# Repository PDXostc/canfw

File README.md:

# CAN FIREWALL

There are two tables, IVI2VEH and VEH2IVI, specifiying rules for
traffic going from the IVI to the vehicle and from vehicle to IVI.

Each one of the two tables has a number of rules.

Each rule has a numberic ID. Rules are executed in order of ascending IDs.

Each rule has an Frame ID mask and a Frame ID filter, applied
according to the standard CAN bus filter principle, as described 
[here](http://www.cse.dmu.ac.uk/~eg/tele/CanbusIDandMask.html).

Below is pseudo code for frame processing.

    process_frame(frame_id, payload) {

      // Traverse all rules
      for (i in rules) {
	    masked_id = (frame_id & rules[i].id_mask);

	    // If the masked out ID is 0, we have a hit. Process
        if (!masked_id) {
	      process(frame_id, input, rules[i].action,
		          rules[i].id_operand, rules[i].data_operand);
	      return;
	    }

        // Check if we have a hit on the masked ID and the
		// ID filter.
	    // If so, we have a hit and will process
	    if (masked_id & rules[i].id_filter) {
	      process(frame_id, input, rules[i].action,
		          rules[i].id_operand, rules[i].data_operand);
	      return;
	    }

        // No hit. Try next rule
	  }

	  // No rule matched. Forward unmodified frame
      process(frame_id, input, ID_AND_DATA_AND,
	          0xFFFFFFFF, 0xFFFFFFFFFFFFFFFF);

	  return ok;
    }

Below is an example of a rule table.

ID | IdMask     |   IdFilter | Action          | IdOperand  | DataOperand        |
---|------------|------------|-----------------|------------|--------------------|
1  | 0xFFFFFFFF | 0x00000012 | ID_AND_DATA_OR  | 0x00FFFFFF | 0x000000FFFFFFFFFF |
2  | 0xFFFFFFF0 | 0x00000120 | ID_SET_DATA_SET | 0x01234567 | 0x0123456780ABCDEF |
99 | 0x00000000 | 0x00000000 | BLOCK           | 0x00000000 | 0x0000000000000000 |

* **RULE 1**<br>
  Rule ID 1 specifies will filter out the lower all bits of the CAN
  frame ID and match those against the specific ID 0x12, thus intercepting
  all CAN frames with the exact ID of 0x00000012.<br>
  An intercepted frame will be forwarded to the other side after ANDing
  the incoming Frame ID with ```0x00FFFFFF```, and then ORing the
  data payload with ```0x000000FFFFFFFFFF```.<br>
  Once the intercepted frame has been forwarded, the next frame is processed.

* **RULE 2**<br>

  Rule ID 2 is evaluated for all frames not intercepted by Rule 1 above.
  The rule will mask the incoming CAN frame ID against ```0xFFFFFFF0```
  and filter the result against ```0x00000120```, intercepting all
  CAN frames between ```0x00000120``` and ```0x0000012F```.<br>
  For each frame intercetpted by rule 2, a fixed frame will be sent to the other side
  with the frame ID ```0x01234567``` and payload ```0x0123456780ABCDEF```.

* **RULE 99**<br>
  Rule 99, a catch all, has a mask that intercepts all frames not intercepted
  by rule 1 or 2. Since the mask is ```0x00000000```, the filter will not be
  used since there no bits will pass the mask to be applied to the filter.<br>
  Rule 99 will block the frame and not send anything to the other side.<br>
  The modification bitmasks for the frame ID and data payload are unused 
  for blocking rules.

Please see presentation under doc for further details.

Hardware Details and Data sheets:
AT32UC3C2512C Datasheet http://www.mouser.com/ds/2/36/doc32117-74889.pdf

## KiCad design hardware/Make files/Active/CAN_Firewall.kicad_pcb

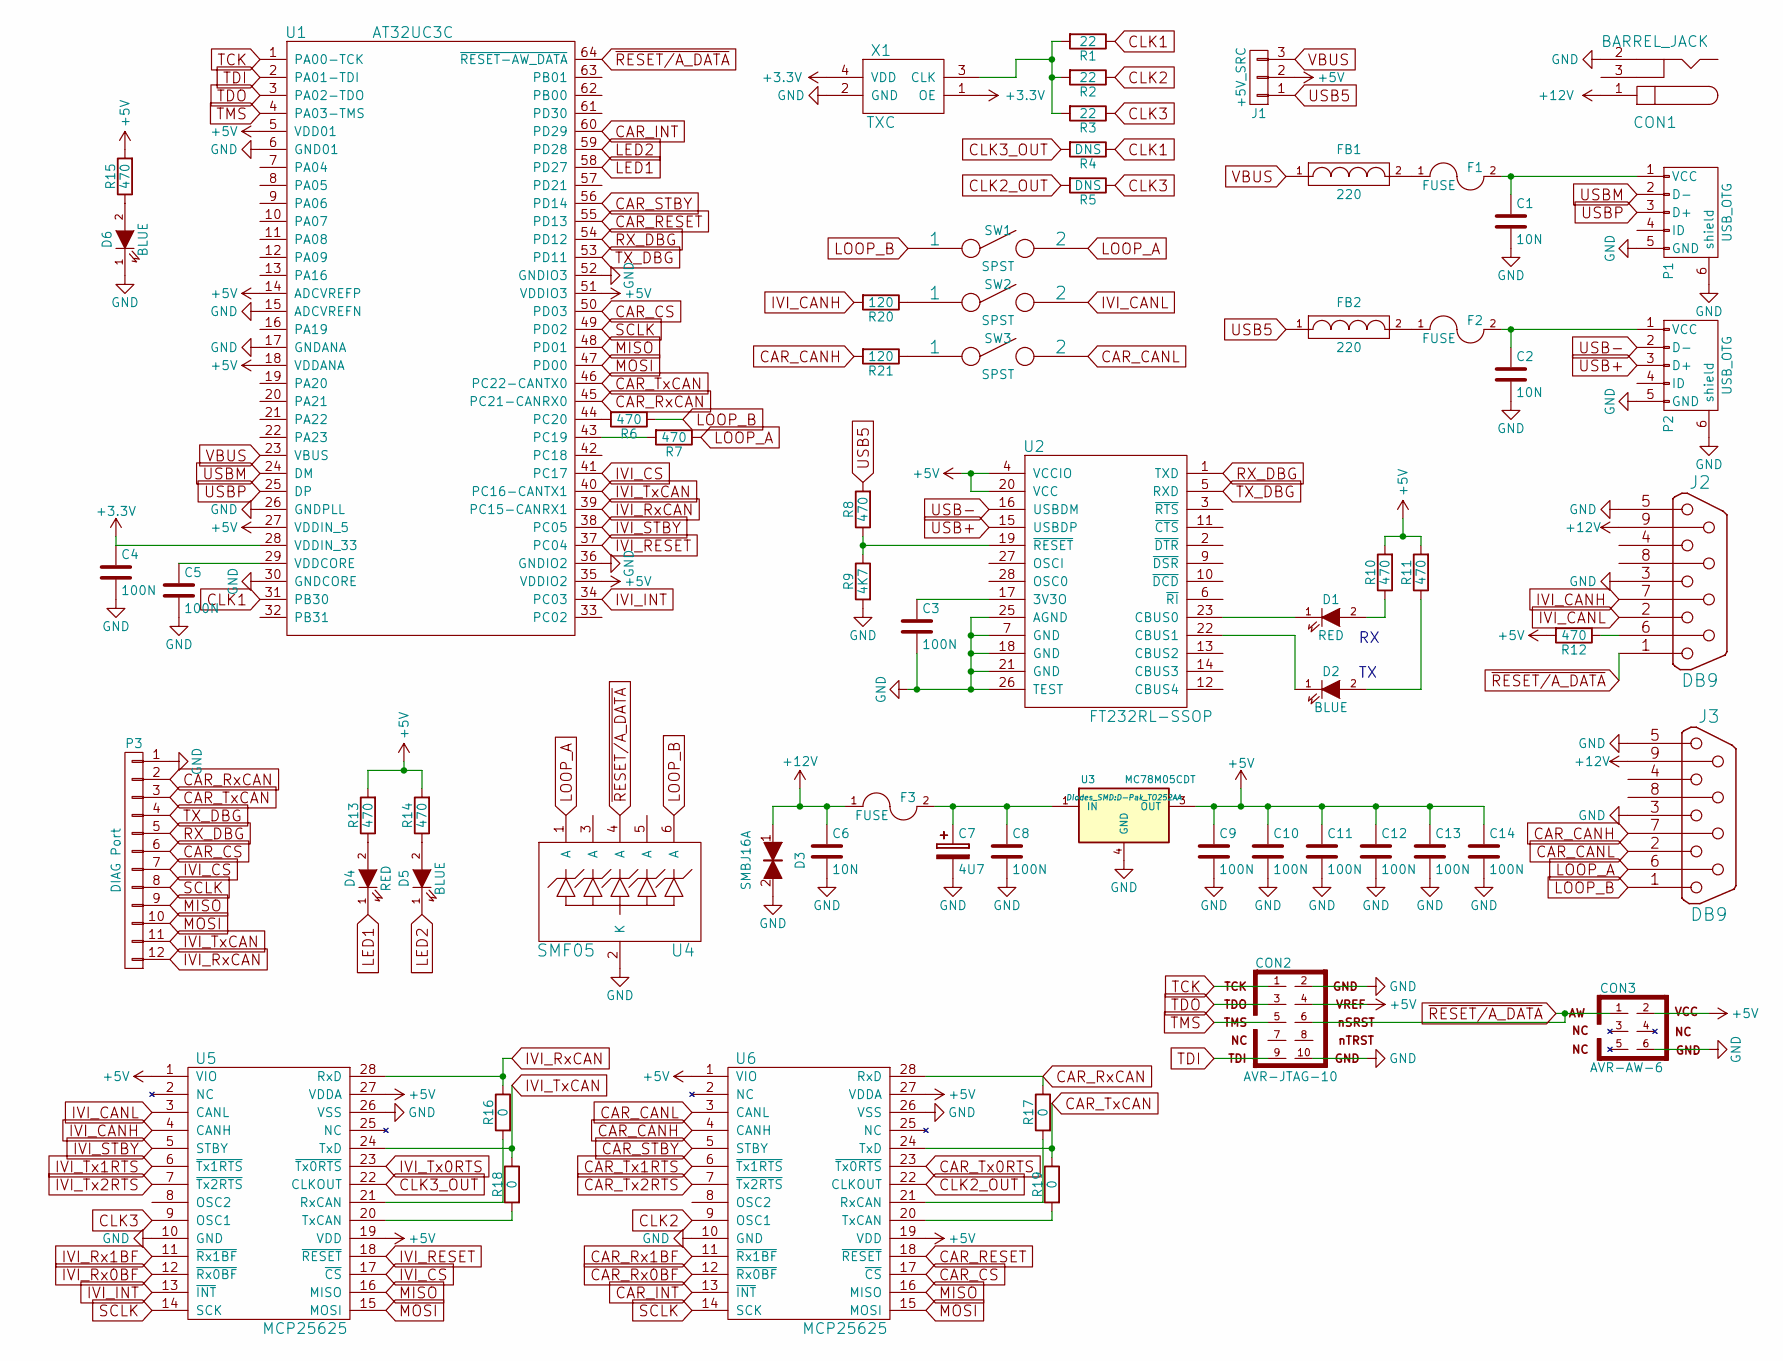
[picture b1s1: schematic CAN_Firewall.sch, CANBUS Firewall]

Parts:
C1, C2, C6: 10N; R_0603_sm
C3, C4, C5, C8, C9, C10, C11, C12, C13, C14: 100N; R_0603_sm
C7: 4U7; TantalC_SizeA_EIA-3216_Reflow
CON1: BARREL_JACK
CON2: AVR-JTAG-10; Socket_Strip_Straight_2x05
CON3: AVR-AW-6; Socket_Strip_Straight_2x03
D1, D4: RED; Diode_0805_12
D2, D5, D6: BLUE; Diode_0805_12
D3: SMBJ16A; SMB_Handsoldering
F1, F2, F3: FUSE; R_1210_SM
FB1, FB2: 220; Diode_0805_12_SM
J1: +5V_SRC; Socket_Strip_Straight_1x03
J2, J3: DB9; DB9F_CI
P1, P2: USB_OTG; USB_Micro-B-DX4R005JJ2R1800
P3: DIAG Port; Socket_Strip_Straight_1x12
R1, R2, R3: 22; R_0603_sm
R4, R5: DNS; R_0603_sm
R6, R7, R8, R10, R11, R12, R13, R14, R15: 470; R_0603_sm
R9: 4K7; R_0603_sm
R16, R17, R18, R19: 0; R_0603_sm
R20, R21: 120; R_0603_sm
SW1, SW2, SW3: SPST; SW_SPST_FSMSM_SM
U1: AT32UC3C; LQFP-64_10x10mm_Pitch0.5mm
U2: FT232RL-SSOP; SSOP-28_5.3x10.2mm_Pitch0.65mm
U3: MC78M05CDT; D-Pak_TO252AA
U4: SMF05; SC-70-6
U5, U6: MCP25625; SSOP-28_5.3x10.2mm_Pitch0.65mm
X1: TXC

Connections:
+3V3: C4.1, U1.28 (VDDIN_33), X1.1 (OE), X1.4 (VDD)
+5V: C9.1, C10.1, C11.1, C12.1, C13.1, C14.1, CON2.4, CON3.2, J1.2, R10.2, R11.2, R12.2, R13.2, R14.2, R15.2, U1.5 (VDD01), U1.14 (ADCVREFP), U1.18 (VDDANA), U1.27 (VDDIN_5), U1.35 (VDDIO2), U1.51 (VDDIO3), U2.4 (VCCIO), U2.20 (VCC), U3.3 (OUT), U5.1 (VIO), U5.19 (VDD), U5.27 (VDDA), U6.1 (VIO), U6.19 (VDD), U6.27 (VDDA)
+12V: C6.1, CON1.1, D3.1, F3.1, J2.9, J3.9
CAR_CANH: J3.7, R21.2, U6.4 (CANH)
CAR_CANL: J3.2, SW3.2, U6.3 (CANL)
CAR_CS: P3.6, U1.50 (PD03), U6.17 (~CS)
CAR_INT: U1.60 (PD29), U6.13 (~INT)
CAR_RESET: U1.55 (PD13), U6.18 (~RESET)
CAR_Rx0BF: U6.12 (~Rx0BF)
CAR_Rx1BF: U6.11 (~Rx1BF)
CAR_RxCAN: P3.2, R17.1, U1.45 (PC21-CANRX0), U6.28 (RxD)
CAR_STBY: U1.56 (PD14), U6.5 (STBY)
CAR_Tx0RTS: U6.23 (~Tx0RTS)
CAR_Tx1RTS: U6.6 (~Tx1RTS)
CAR_Tx2RTS: U6.7 (~Tx2RTS)
CAR_TxCAN: P3.3, R19.1, U1.46 (PC22-CANTX0), U6.24 (TxD)
CLK1: R1.1, R4.1, U1.31 (PB30)
CLK2: R2.1, U6.9 (OSC1)
CLK2_OUT: R5.2, U6.22 (CLKOUT)
CLK3: R3.1, R5.1, U5.9 (OSC1)
CLK3_OUT: R4.2, U5.22 (CLKOUT)
GND: C1.2, C2.2, C3.2, C4.2, C5.2, C6.2, C7.2, C8.2, C9.2, C10.2, C11.2, C12.2, C13.2, C14.2, CON1.2, CON2.2, CON2.10, CON3.6, D3.2, D6.1 (K), J2.3, J2.5, J3.3, J3.5, P1.5 (GND), P1.6 (shield), P2.5 (GND), P2.6 (shield), P3.1, R9.2, U1.6 (GND01), U1.15 (ADCVREFN), U1.17 (GNDANA), U1.26 (GNDPLL), U1.30 (GNDCORE), U1.36 (GNDIO2), U1.52 (GNDIO3), U2.7 (GND), U2.18 (GND), U2.21 (GND), U2.25 (AGND), U2.26 (TEST), U3.4 (GND), U4.2 (K), U5.10 (GND), U5.26 (VSS), U6.10 (GND), U6.26 (VSS), X1.2 (GND)
IVI_CANH: J2.7, R20.2, U5.4 (CANH)
IVI_CANL: J2.2, SW2.2, U5.3 (CANL)
IVI_CS: P3.7, U1.41 (PC17), U5.17 (~CS)
IVI_INT: U1.34 (PC03), U5.13 (~INT)
IVI_RESET: U1.37 (PC04), U5.18 (~RESET)
IVI_Rx0BF: U5.12 (~Rx0BF)
IVI_Rx1BF: U5.11 (~Rx1BF)
IVI_RxCAN: P3.12, R16.1, U1.39 (PC15-CANRX1), U5.28 (RxD)
IVI_STBY: U1.38 (PC05), U5.5 (STBY)
IVI_Tx0RTS: U5.23 (~Tx0RTS)
IVI_Tx1RTS: U5.6 (~Tx1RTS)
IVI_Tx2RTS: U5.7 (~Tx2RTS)
IVI_TxCAN: P3.11, R18.1, U1.40 (PC16-CANTX1), U5.24 (TxD)
LED1: D4.1 (K), U1.58 (PD27)
LED2: D5.1 (K), U1.59 (PD28)
LOOP_A: J3.6, R7.1, SW1.2, U4.1 (A)
LOOP_B: J3.1, R6.1, SW1.1, U4.6 (A)
MISO: P3.9, U1.48 (PD01), U5.16 (MISO), U6.16 (MISO)
MOSI: P3.10, U1.47 (PD00), U5.15 (MOSI), U6.15 (MOSI)
unnamed: C1.1, F1.2, P1.1 (VCC)
unnamed: C2.1, F2.2, P2.1 (VCC)
unnamed: C3.1, U2.17 (3V3O)
unnamed: C5.1, U1.29 (VDDCORE)
unnamed: C7.1, C8.1, F3.2, U3.1 (IN)
unnamed: D1.1 (K), U2.23 (CBUS0)
unnamed: D1.2 (A), R10.1
unnamed: D2.1 (K), U2.22 (CBUS1)
unnamed: D2.2 (A), R11.1
unnamed: D4.2 (A), R13.1
unnamed: D5.2 (A), R14.1
unnamed: D6.2 (A), R15.1
unnamed: F1.1, FB1.2
unnamed: F2.1, FB2.2
unnamed: J2.6, R12.1
unnamed: R1.2, R2.2, R3.2, X1.3 (CLK)
unnamed: R6.2, U1.44 (PC20)
unnamed: R7.2, U1.43 (PC19)
unnamed: R8.1, R9.1, U2.19 (~RESET)
unnamed: R16.2, U5.21 (RxCAN)
unnamed: R17.2, U6.21 (RxCAN)
unnamed: R18.2, U5.20 (TxCAN)
unnamed: R19.2, U6.20 (TxCAN)
unnamed: R20.1, SW2.1
unnamed: R21.1, SW3.1
RX_DBG: P3.5, U1.54 (PD12), U2.1 (TXD)
SCLK: P3.8, U1.49 (PD02), U5.14 (SCK), U6.14 (SCK)
TCK: CON2.1, U1.1 (PA00-TCK)
TDI: CON2.9, U1.2 (PA01-TDI)
TDO: CON2.3, U1.3 (PA02-TDO)
TMS: CON2.5, U1.4 (PA03-TMS)
TX_DBG: P3.4, U1.53 (PD11), U2.5 (RXD)
USB5: FB2.1, J1.1, R8.2
USB+: P2.3 (D+), U2.15 (USBDP)
USB-: P2.2 (D-), U2.16 (USBDM)
USBM: P1.2 (D-), U1.24 (DM)
USBP: P1.3 (D+), U1.25 (DP)
VBUS: FB1.1, J1.3, U1.23 (VBUS)
~RESET/A_DATA: CON2.6, CON3.1, J2.1, U1.64 (~RESET-AW_DATA), U4.4 (A)

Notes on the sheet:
RX TX

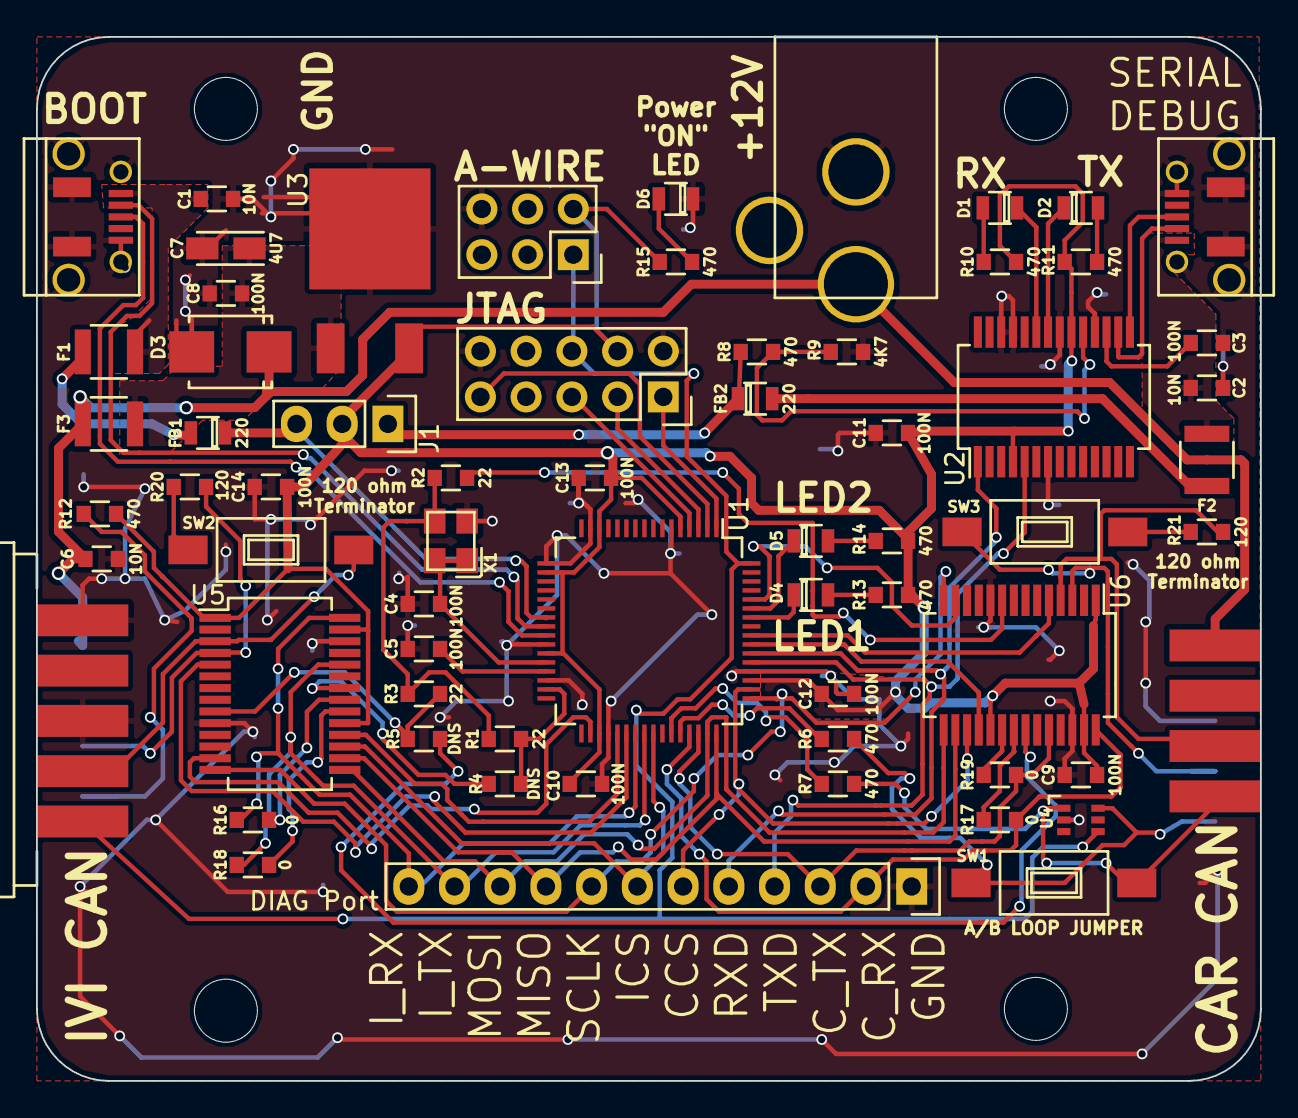
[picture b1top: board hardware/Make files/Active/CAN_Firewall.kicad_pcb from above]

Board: 2 copper layers, 68.0 x 58.0 mm, 65 parts (1 on the bottom side), 70 nets.

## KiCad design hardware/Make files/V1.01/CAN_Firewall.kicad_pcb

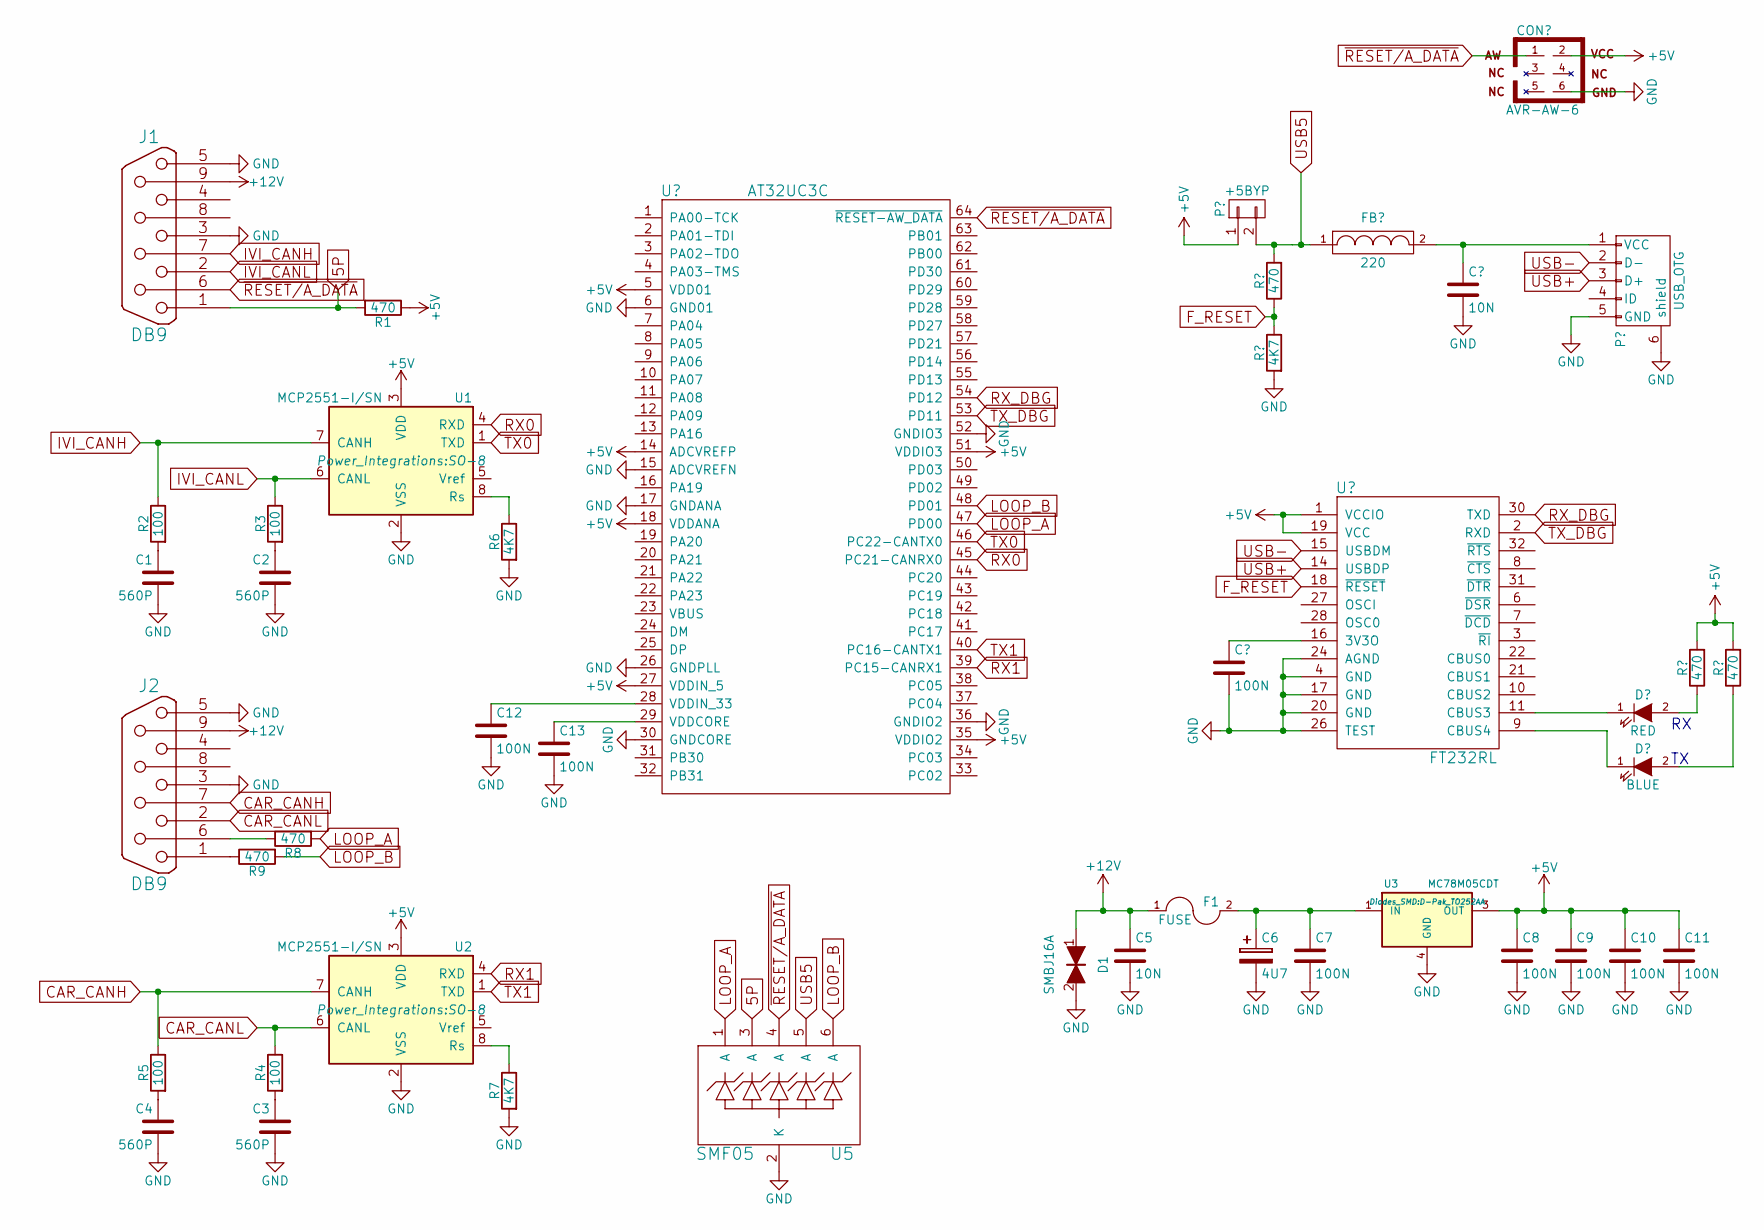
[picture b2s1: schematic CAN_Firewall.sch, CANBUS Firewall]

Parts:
C1, C2, C3, C4: 560P; R_0603_sm
C5: 10N; R_0603_sm
C6: 4U7; TantalC_SizeA_EIA-3216_Reflow
C7, C8, C9, C10, C11, C12, C13: 100N; R_0603_sm
D1: SMBJ16A; Diode-SMB_Standard
F1: FUSE; R_1210_SM
J1, J2: DB9; DB9F_CI
R1, R8, R9: 470; R_0603_sm
R2, R3, R4, R5: 100; R_0603_sm
R6, R7: 4K7; R_0603_sm
U1, U2: MCP2551-I/SN; SO-8
U3: MC78M05CDT; D-Pak_TO252AA
U5: SMF05; SC-70-6

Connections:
5P: J1.1, R1.2, U5.3 (A)
+5V: C8.1, C9.1, C10.1, C11.1, R1.1, U1.3 (VDD), U2.3 (VDD), U3.3 (OUT); also elsewhere on the board
+12V: C5.1, D1.1, F1.1, J1.9, J2.9; also elsewhere on the board
A_DATAOUT: J1.8, U5.5 (A); also elsewhere on the board
CAR_CANH: J2.7, R5.1, U2.7 (CANH)
CAR_CANL: J2.2, R4.1, U2.6 (CANL)
GND: C1.2, C2.2, C3.2, C4.2, C5.2, C6.2, C7.2, C8.2, C9.2, C10.2, C11.2, C12.2, C13.2, D1.2, J1.3, J1.5, J2.3, J2.5, R6.2, R7.2, U1.2 (VSS), U2.2 (VSS), U3.4 (GND), U5.2 (K); also elsewhere on the board
IVI_CANH: J1.7, R2.1, U1.7 (CANH)
IVI_CANL: J1.2, R3.1, U1.6 (CANL)
LOOP_A: R8.2, U5.1 (A); also elsewhere on the board
LOOP_B: R9.2, U5.6 (A); also elsewhere on the board
unnamed: C1.1, R2.2
unnamed: C2.1, R3.2
unnamed: C3.1, R4.2
unnamed: C4.1, R5.2
unnamed: C6.1, C7.1, F1.2, U3.1 (IN)
unnamed 16: C12.1; also elsewhere on the board
unnamed 17: C13.1; also elsewhere on the board
unnamed: J2.1, R9.1
unnamed: J2.6, R8.1
unnamed: R6.1, U1.8 (Rs)
unnamed: R7.1, U2.8 (Rs)
RX0: U1.4 (RXD); also elsewhere on the board
RX1: U2.4 (RXD); also elsewhere on the board
TX0: U1.1 (TXD); also elsewhere on the board
TX1: U2.1 (TXD); also elsewhere on the board
~RESET/A_DATA: J1.6, U5.4 (A); also elsewhere on the board

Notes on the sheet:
RX TX

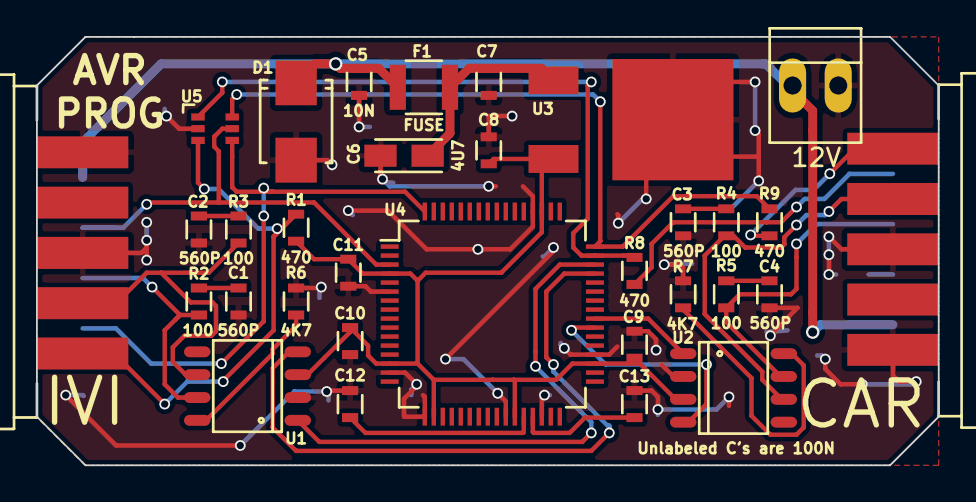
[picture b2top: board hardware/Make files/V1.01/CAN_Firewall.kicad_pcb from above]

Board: 2 copper layers, 50.1 x 23.8 mm, 32 parts (0 on the bottom side), 27 nets.

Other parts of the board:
12V: PINHEAD1-2
U4: AT32UC3C; LQFP-64_10x10mm_Pitch0.5mm

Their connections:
+5V: U4.4, U4.14, U4.18, U4.27, U4.35, U4.51; also elsewhere on the board
+12V: 12V.1; also elsewhere on the board
A_DATAOUT: U4.3; also elsewhere on the board
GND: 12V.2, U4.6, U4.15, U4.17, U4.26, U4.30, U4.36, U4.52; also elsewhere on the board
LOOP_A: U4.47; also elsewhere on the board
LOOP_B: U4.48; also elsewhere on the board
unnamed 16: U4.28; also elsewhere on the board
unnamed 17: U4.29; also elsewhere on the board
RX0: U4.45; also elsewhere on the board
RX1: U4.39; also elsewhere on the board
TX0: U4.46; also elsewhere on the board
TX1: U4.40; also elsewhere on the board
~RESET/A_DATA: U4.64; also elsewhere on the board

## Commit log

2015-08-11 First README.md stab
2015-08-11 Initial version of presentation and DRD
2015-08-11 Removed trailing cruft
2015-08-11 Added PDF version of presentation
2015-08-11 Added first spin of hardware
2015-08-13 Including all files from jesse
    Updated with my current changes since I sent the HW package over thumb
    drive to Magnus.
    Did some V1->V2 cleanup with files and folders
2015-08-13 Refined git ignore
    now ignores only pfd's in the research folder. allows sharing pdfs in
    "project shares"
    Updated readme with AT32UC3C Data sheet link
2015-08-13 V1.1 Devlopment
    Created teh V1.1 hardware files. The Hardware patch for V1 will follow
    this design.
2015-08-14 V1.1 Diag port improved
    added another resistor in the Loop B input, to facilitate a "bypass
    mode" in conjunction with a "rule learn mode".
2015-08-24 exploring the fixes for the proto
    made a rudimentary design to copy when building the CBFW proto, as it
    requires modifications.
2015-08-24 Created CBFW Hardware Overview
    Made a HW project visio
2015-08-26 Modified with HMAC-SHA256 signature
2015-08-28 Fixed some minor bugs in payload calculation
2015-08-31 Corrected 320 bit HMAC signature to 256 bit signature
2015-08-31 Little endian of all bitfields. Fixed HMAC length
    All multi-frame bitfields are now little endian to facilitate easy roll
    out in memory.
    Removed unused1 and expanded HMAC to 256 bits (was 240 bits)
2015-09-08 Cleanup of files, V1.1 Schematic Dev
    Cleaned up files and folders
    dev of new hardware
2015-09-10 V1.1 layout pass complete
2015-09-10 folders updated for another subrev of PCB
2015-09-10 V1.11 Schematic and PCB layout
2015-09-10 V1.11
2015-09-14 V1.11 Proofed
    Ready to order
2015-09-24 git ignore
2015-10-14 Post build learnings and publications
2015-10-15 Updated logo and copyright
2015-10-16 Fixed slideshow transition timing issues
2015-10-26 Prep for next rev
    found a HW flaw, made fixes
2015-10-26 Fixed CanH-CanL swap
2015-11-03 Moved CAR Interupt signal to different Pin
    Steve needed the car side can controller interupt signal to go to a
    different pin because of some inherent traits of the original pin
2015-12-17 progress towards V1.2
